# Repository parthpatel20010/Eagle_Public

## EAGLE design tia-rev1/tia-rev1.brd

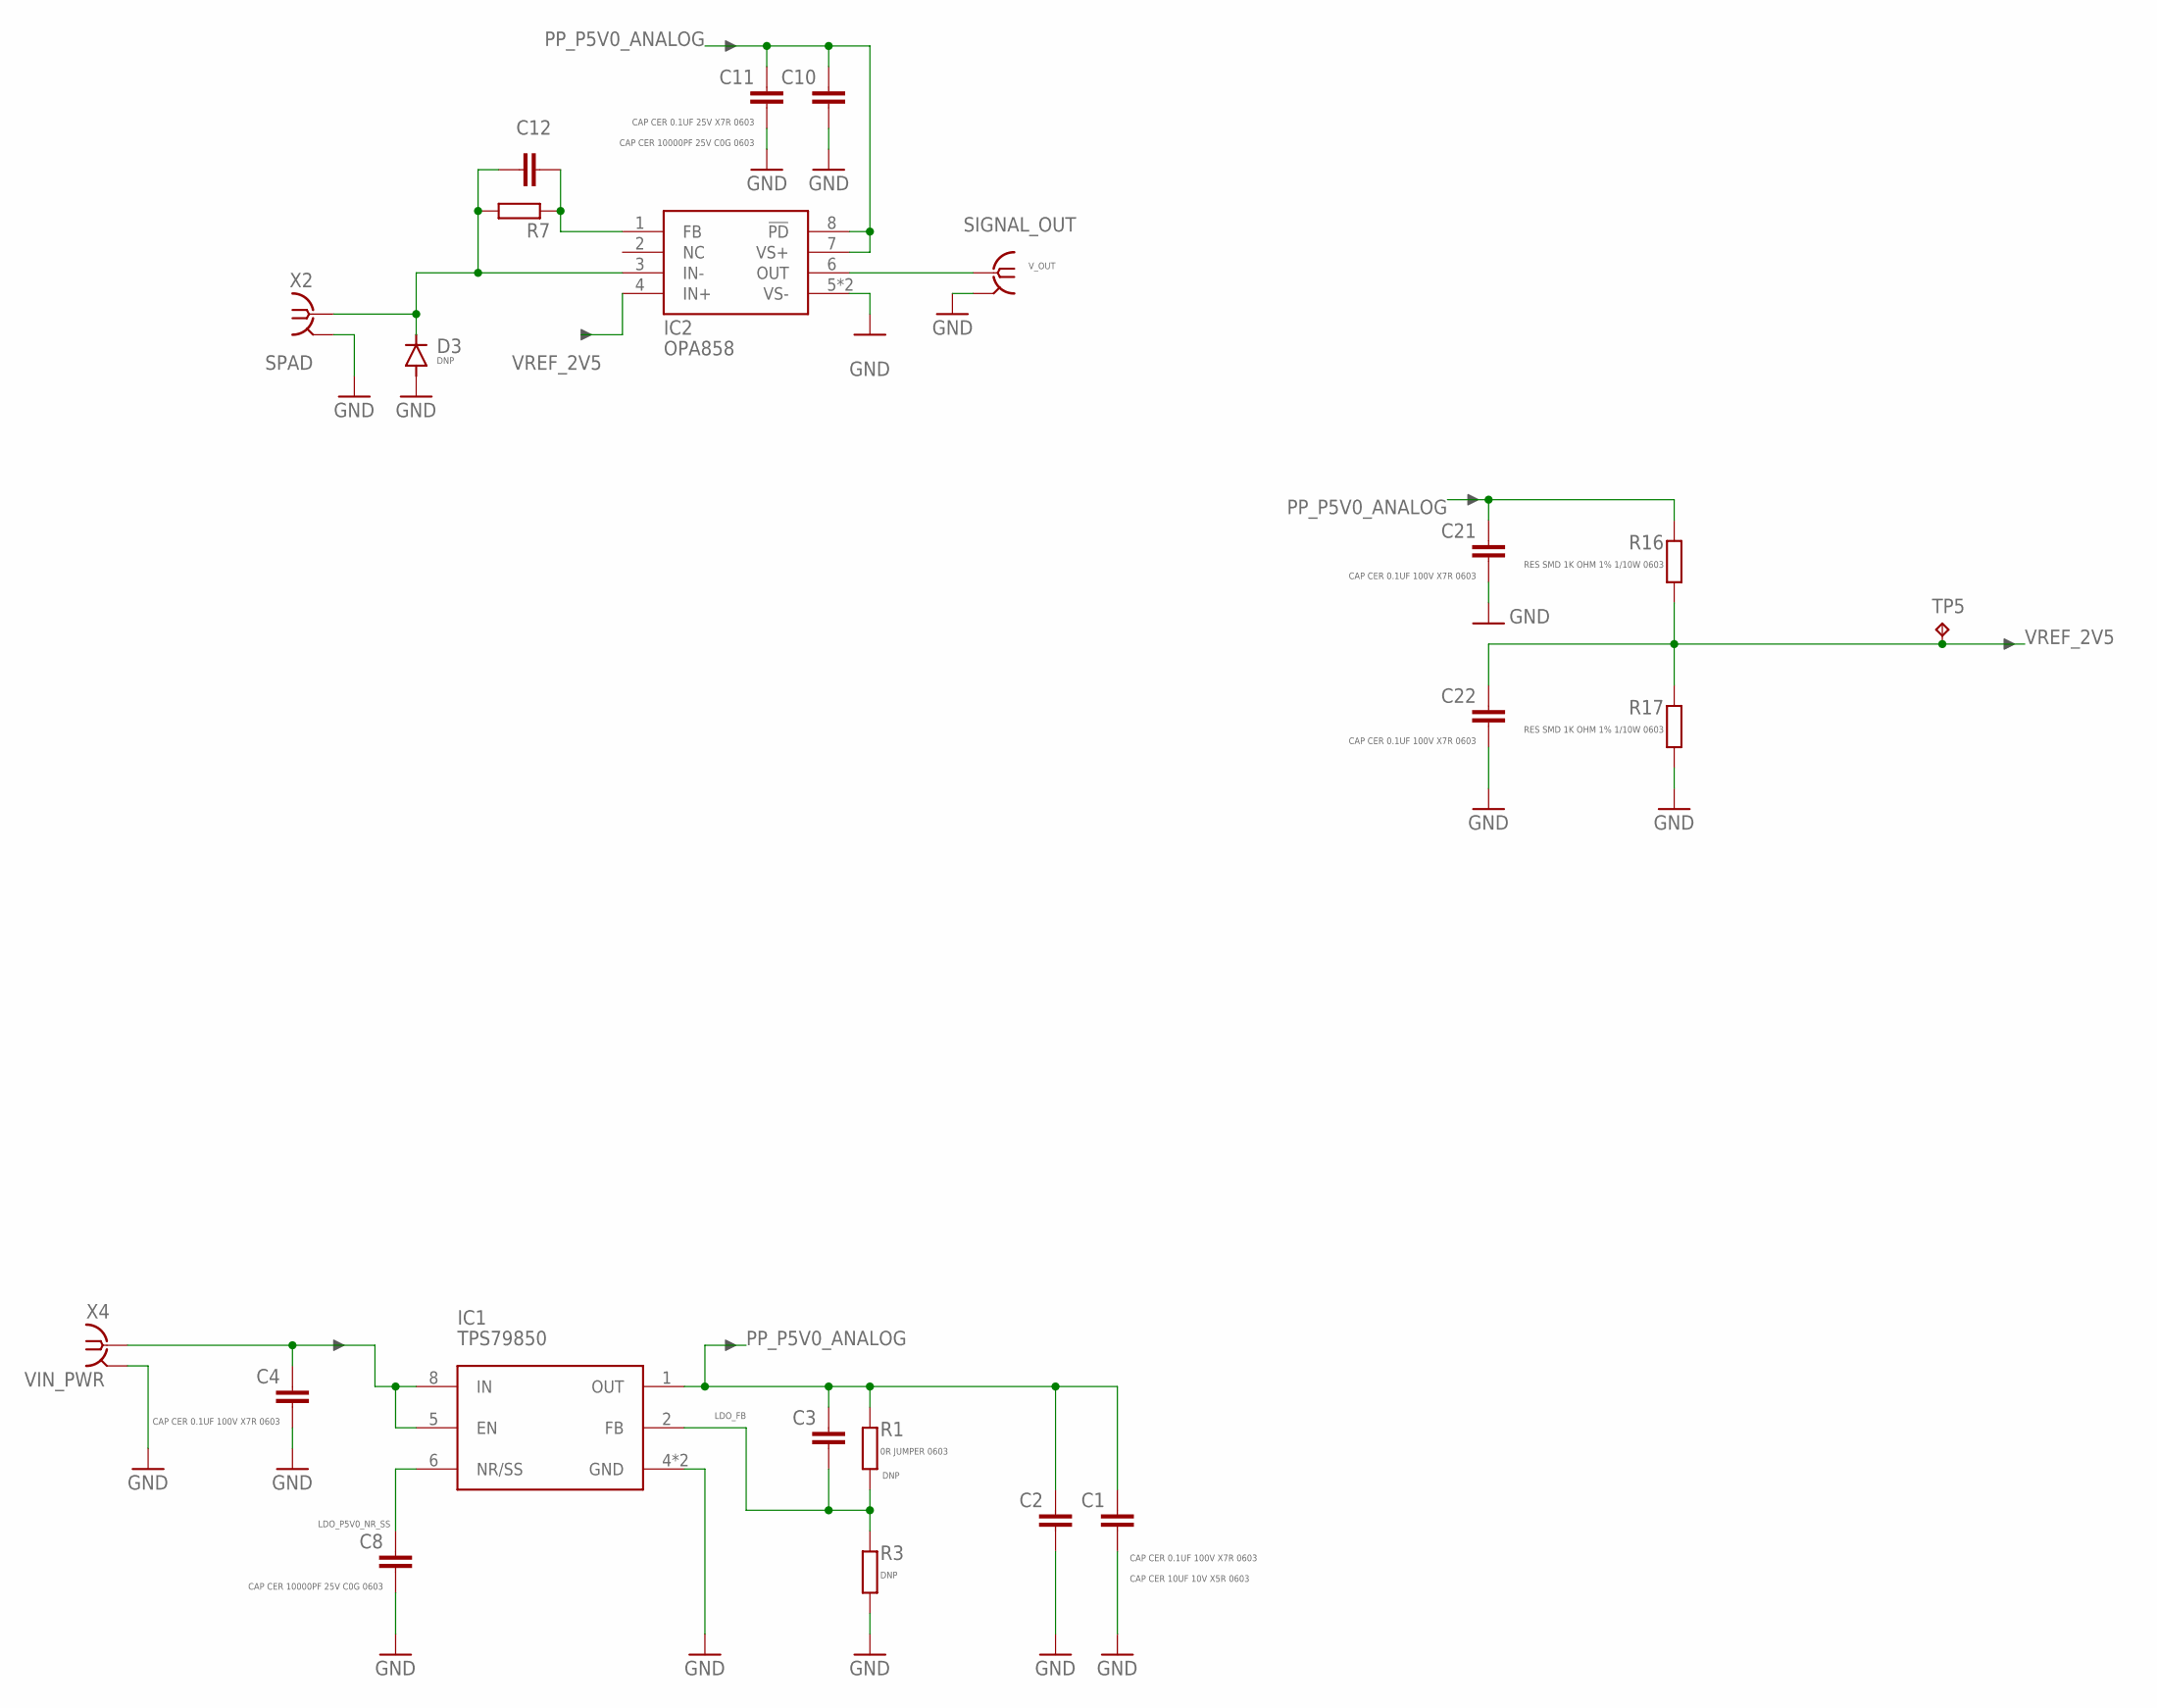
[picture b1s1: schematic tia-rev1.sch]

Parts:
C1: CAP CER 10UF 10V X5R 0603; C0603
C2, C4, C21, C22: CAP CER 0.1UF 100V X7R 0603; C0603
C3: DNP; C0603
C8, C10: CAP CER 10000PF 25V C0G 0603; C0603
C11, C12: CAP CER 0.1UF 25V X7R 0603; C0603
D3: DNP; SOD323-W
IC1: TPS79850; MSOP-8_POWER_PAD
IC2: OPA858; WSON8
R1: 0R JUMPER 0603; R0603
R3, R7: DNP; R0603
R16, R17: RES SMD 1K OHM 1% 1/10W 0603; R0603
TP5: TPTP10R; TP10R
X2: SPAD; J502-ND-142-0701-881/886
X3: SIGNAL_OUT; MMCX-J-P-X-ST-EM1-MKT
X4: VIN_PWR; MMCX-J-P-X-ST-EM1-MKT

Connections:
GND: C1.2, C2.2, C4.2, C8.2, C10.2, C11.2, C21.2, C22.2, D3.A, IC1.4 (GND), IC1.PAD (GND), IC2.5 (VS-), IC2.PAD (VS-), R3.2, R17.1, X2.G@1 (GND), X2.G@2 (GND), X2.G@3 (GND), X2.G@4 (GND), X3.2@1 (GND), X3.2@2 (GND), X3.2@3 (GND), X3.2@4 (GND), X4.2@1 (GND), X4.2@2 (GND), X4.2@3 (GND), X4.2@4 (GND)
IN-: C12.1, D3.C, IC2.3 (IN-), R7.1, X2.1
LDO_FB: C3.2, IC1.2 (FB), R1.1, R3.1
LDO_IN/EN: C4.1, IC1.5 (EN), IC1.8 (IN), X4.1
LDO_P5V0_NR_SS: C8.1, IC1.6 (NR/SS)
PP_P5V0_ANALOG: C1.1, C2.1, C3.1, C10.1, C11.1, C21.1, IC1.1 (OUT), IC2.7 (VS+), IC2.8 (!PD), R1.2, R16.2
TIA_FB: C12.2, IC2.1 (FB), R7.2
VREF_2V5: C22.1, R16.1, R17.2, TP5.TP
V_OUT: IC2.6 (OUT), X3.1

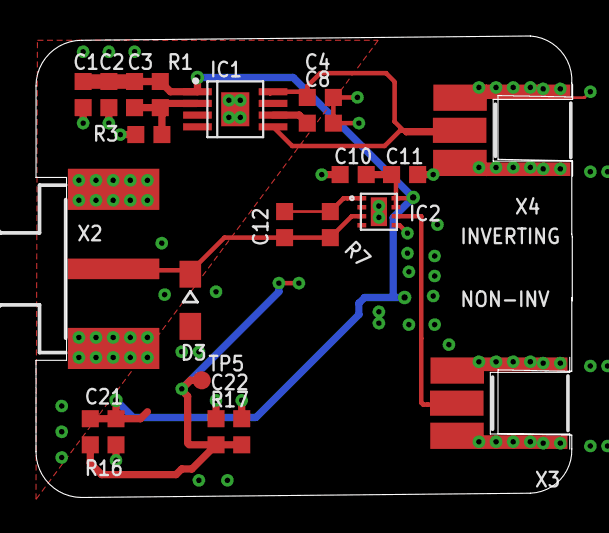
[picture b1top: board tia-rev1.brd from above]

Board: 4 copper layers, 29.8 x 25.6 mm, 22 parts (0 on the bottom side), 9 nets.

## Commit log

2021-08-08 Added tia proj
2021-08-08 deleted extra files
2021-08-09 newest version
2021-08-09 newest version(again
